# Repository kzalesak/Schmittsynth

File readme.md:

# Schmitt Synth - a digital logic synthesizer

A simple square-wave synthesizer circuit using inverting gates (Logical NOT, Schmitt triggers) in the 40106 Integrated Circuit and a few discrete components. The KiCAD schematic, Printed Circuit Board (PCB) and a cached library are provided.
This project was developed for the University College London branch of Engineers Without Borders as a basis for a workshop.

**DEPRECATION NOTE**

**This project is deprecated - please use the upgraded version, [Digisynth](https://github.com/kzalesak/Digisynth), available at https://github.com/kzalesak/Digisynth**

## Getting Started

### Prerequisites

In order to view and edit the files you are going to need the open source circuitry tool KiCAD, available from:

```
http://kicad-pcb.org/
```

### Installing

After installing KiCAD, the project should simply open upon clicking on the 40106_synth.pro file. From here, you can view the schematic and PCB Layout

## How does the circuit work?

The circuit works by connecting a Schmitt inverter (NOT Gate) in a feedback loop. The inverter outputs a HIGH voltage on its output pin when there is LOW voltage on its input pin and vice versa. By connecting a capacitor between the input pin and ground, we control how long it takes for a voltage change to propagate from the output pin to the input pin, effectively controlling our oscillation frequency. This is proportional to the capacity of our capacitor, as a larger capacitor will take longer to charge. We further connect the input and output pins via a variable resistor (potentiometer), thereby controlling how much current flows between the output pins and to the capacitor, limiting how fast it can charge. We thus obtain an oscillating circuit in which we can control the frequency by changing the capacitance and resistance of the respective components. 

## How to connect your assembled synthesizer

### Basic setup
In order to operate your synth, you need to connect one of the inverting gates to (see under text for demo connections):
1. **a capacitor on its input pin** - you can do this by placing a capacitor between the female pin header below or above the 40106 IC (black box with legs in the middle of the board). Note that cylindrical capacitors with a stripe (electrolytic) are polarized, and the stripe should be connected to ground, as in the example setup. If your capacitor is soldered on, simply choose the desired gate.
2. **a resistance between the input and output pin of the gate (not OUTPUT)** - this allows you to control the tone, as well as ensures the sound is in the audible range and not ultrasound, which annoys animals. You can use a potentiometer or the photoresistor on the board, or use wires to connect to a resistive material, like a pencil drawing or a piece of fruit. You can also connect multiple resistors in series or parallel, to experiment with different effects.
3. **appropriate sound OUTPUT pin to the voltage divider IN pin** - use the same letter as the one next to the gate. To visualise what is happening, you can choose a large value capacitor (>100uF) and connect the OUTPUT pin to the LED instead. The voltage divider is required to bring down the voltage to standard audio levels (9V -> \~1.5V).

4. **voltage divider DIV pin to left or right channel** to use both, connect them together.

A sample setup using a potentiometer and gate __D__ is shown here:

### Oscillator sync
Oscillators can be set up in a "synced" mode by having one oscillator control the second one. This is achieved by connecting one oscillator output (or input) pin through a diode to the input pin of the other, periodically bringing the input pin of the second one high, thus turning its output low. The first one then controls the pitch of the tone and the second one controls timbre, or the color of the sound. It is necessary that the frequency of the first one is sufficiently lower then the second one, otherwise the second one will fail to trigger within the necessary time period and the circuit will stay silent. It is thus recommended to use a larger capacitor for the first oscilator and a smaller one for the second.

An example setup using gate __D__ to control gate __F__ is shown here:

### Decay effect
When the decay capacitor is added, an interesting envelope effect upon power off is created, a combination of decreasing volume and increasing frequency. It is recommended that a female pin header is soldered in place of the capacitor allowing a quick change of the capacitor. A large value (>10uF) is necessary for the effect to be strongly apparent. Pay attention to the polarity, the negative lead position is marked white.

This is the decay capacitor on the board:

## Production note

__DO NOT MAKE THIS PCB. IT IS HERE FOR ARCHIVAL PURPOSES. USE THE NEWER [DIGISYNTH](https://github.com/kzalesak/Digisynth) INSTEAD__

## License

This project is licensed under the TAPR Open Hardware License (www.tapr.org/OHL).

## Acknowledgments

I would like to thank Engineers Without Borders for making it possible to run workshops where we built the and explored the circuit.

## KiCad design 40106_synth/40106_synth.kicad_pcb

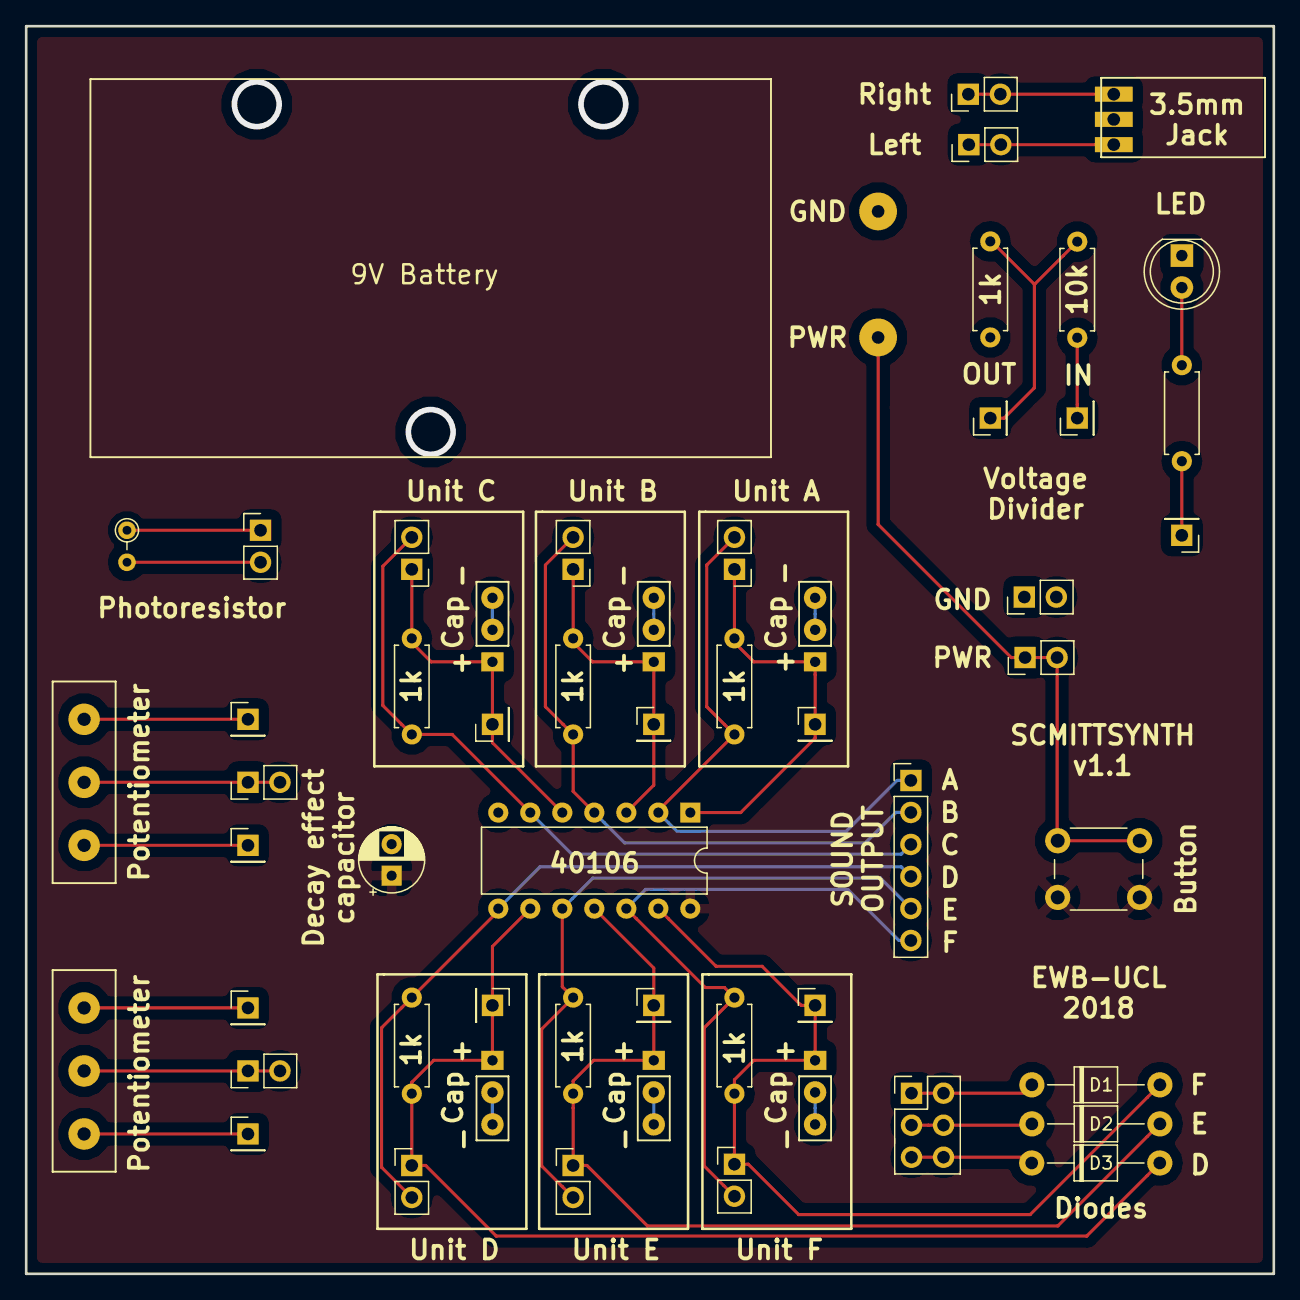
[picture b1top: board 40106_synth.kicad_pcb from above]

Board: 2 copper layers, 99.0 x 99.0 mm, 55 parts (0 on the bottom side), 32 nets.

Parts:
BT1: Battery_Cell; BatteryHolder_COMF_BH9VA_1x6F22(9V)
C1, C2, C3, C4, C5, C6: CP; cap_2+3
C7: CP; CP_Radial_D5.0mm_P2.50mm
D1, D2, D3: D; Diode_P10.16mm_Horizontal
D4: LED; LED_D5.0mm
J1, J4, J7, J8, J11, J12, J19, J23, J24, J25, J26, J30, J31: Conn_01x01; PinHeader_1x01_P2.54mm_Vertical
J2, J3, J5, J9, J13, J14, J18, J21, J22, J27, J28, J29, J101: Conn_01x02; PinHeader_1x02_P2.54mm_Vertical
J16: Conn_02x03_Counter_Clockwise; PinHeader_2x03_P2.54mm_Vertical
J32: Audio-Jack-3; Jack_3.5mm_Boom_Precision_DC-003A
J100: Conn_01x06; PinHeader_1x06_P2.54mm_Vertical
R1, R2, R3, R4, R5, R6, R7, R8, R9: R; R_Axial_DIN0207_L6.3mm_D2.5mm_P7.62mm_Horizontal
R101: R_PHOTO; R_Axial_DIN0204_L3.6mm_D1.6mm_P2.54mm_Vertical
RV1, RV2: POT; SR_PASSIVES_POT_PW1.00_P5.00
SW1: SW_DIP_x02; SW_PUSH_6mm
U1: 40106; DIP-14_W7.62mm

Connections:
/BATT_9V: BT1.1, J18.1, J18.2, SW1.1
/OUTA: J2.2, J100.1, R1.1, U1.2
/OUTB: J3.2, J100.2, R2.1, U1.4
/OUTC: J5.2, J100.3, R3.1, U1.6
/OUTD: J9.2, J100.4, R4.1, U1.8
/OUTE: J13.2, J100.5, R5.1, U1.10
/OUTF: J14.2, J100.6, R6.1, U1.12
/SYN1: C6.1, D1.2, J12.1, J14.1, R6.2, U1.13
/SYN2: C5.1, D2.2, J11.1, J13.1, R5.2, U1.11
/SYN3: C4.1, D3.2, J7.1, J9.1, R4.2, U1.9
GND: BT1.2, C1.2, C2.2, C3.2, C4.2, C5.2, C6.2, C7.2, D4.1, J22.1, J22.2, J32.3, R9.1, U1.7
unnamed: C1.1, J1.1, J2.1, R1.2, U1.1
unnamed: C2.1, J3.1, J8.1, R2.2, U1.3
unnamed: C3.1, J4.1, J5.1, R3.2, U1.5
unnamed: D1.1, J16.1, J16.2
unnamed: D2.1, J16.3, J16.4
unnamed: D3.1, J16.5, J16.6
unnamed: D4.2, R7.1
unnamed: J19.1, RV1.3
unnamed: J21.1, J21.2, RV1.2
unnamed: J23.1, RV1.1
unnamed: J24.1, R7.2
unnamed: J25.1, RV2.3
unnamed: J26.1, R8.2
unnamed: J27.1, J27.2, J32.1
unnamed: J28.1, J28.2, RV2.2
unnamed: J29.1, J29.2, J32.2
unnamed: J30.1, R8.1, R9.2
unnamed: J31.1, RV2.1
unnamed: J101.1, R101.1
unnamed: J101.2, R101.2
PWR: C7.1, SW1.2, U1.14

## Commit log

2018-12-20 Initial commit, v1.1 of board.
2019-01-06 Add licence. Add README. Add model setups. Touch up silkscreen.
2019-01-06 Fix image path
2019-01-06 Resize image
2019-01-06 paragraph add
2019-01-06 Add decay setup
2019-01-06 Add decay setup image
2019-01-07 Typos fix
